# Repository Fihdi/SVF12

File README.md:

# 8hp 12dB/Oct Voltage Controlled state-variable Filter

# Features
- Two  Inputs **IN** (DC-coupled, allows for audio and CV processing)
- Volt per octave Input **V/O**
- Ping Input **PING**
- Self-Resonance switch **FILT/OSC**
- Lowpass **LP** Bandpass **BP** Bandstop(Notch) **BS** and Highpass **HP** outputs 

# Oscillator mode
The module can be switched from Filter mode (Switch in the **FILT** position) to Oscillator mode (Switch in the **OSC** position), turning the module into a musical sine-cosine quadrature VCO. This can produce clean sine waves on the **BP**, **BS** and **LP** outputs with no input, a mode called self-oscillation. The sinusoidal signals of  **BP** and **HP** are phase-shifted 0, 90 and 180 degrees.

.Inverting the **BP** signal and sending it back into a state variable filter it starts to self-oscillate, albeit with no limiting. Switching from **FILT** to **OSC** changes the **RES** knob from a variable voltage divider to an attenuverter with diode-clipping. With a trimmer on the back of the module, the **V/O** input can be tuned to allow for volt per octave tracking

# Ping Input
By sending a rising-edge signal like a Gate or a short Pulse to the **PING** input, the filter core gets excited and creates a damped oscillation. The length of this oscillation is controlled by the resonance (**RES**) setting.

# Power
A standard 10-pin Eurorack power connector is used (Red Stripe indicates -12V (negative twelve volts)). The module is internally running on +/-9V to stabilise the volt per octave tracking.

# Sponsor
A big Thank You to [PCBWay](https://www.pcbway.com) for sponsoring the development and prototyping of this module! They have excellent build quality and I can recommend using their service to build your own projects! I used the "Black" soldermask and white silkscreen and the surface has very deep and glossy black finish.

Simply upload the Gerber and production files for the B-Board and 90% of the circuitry is done. Solder the final through-hole components and tightend the screws and you have a finished Eurorack module, ready to give your sounds a crunchy filter effect.

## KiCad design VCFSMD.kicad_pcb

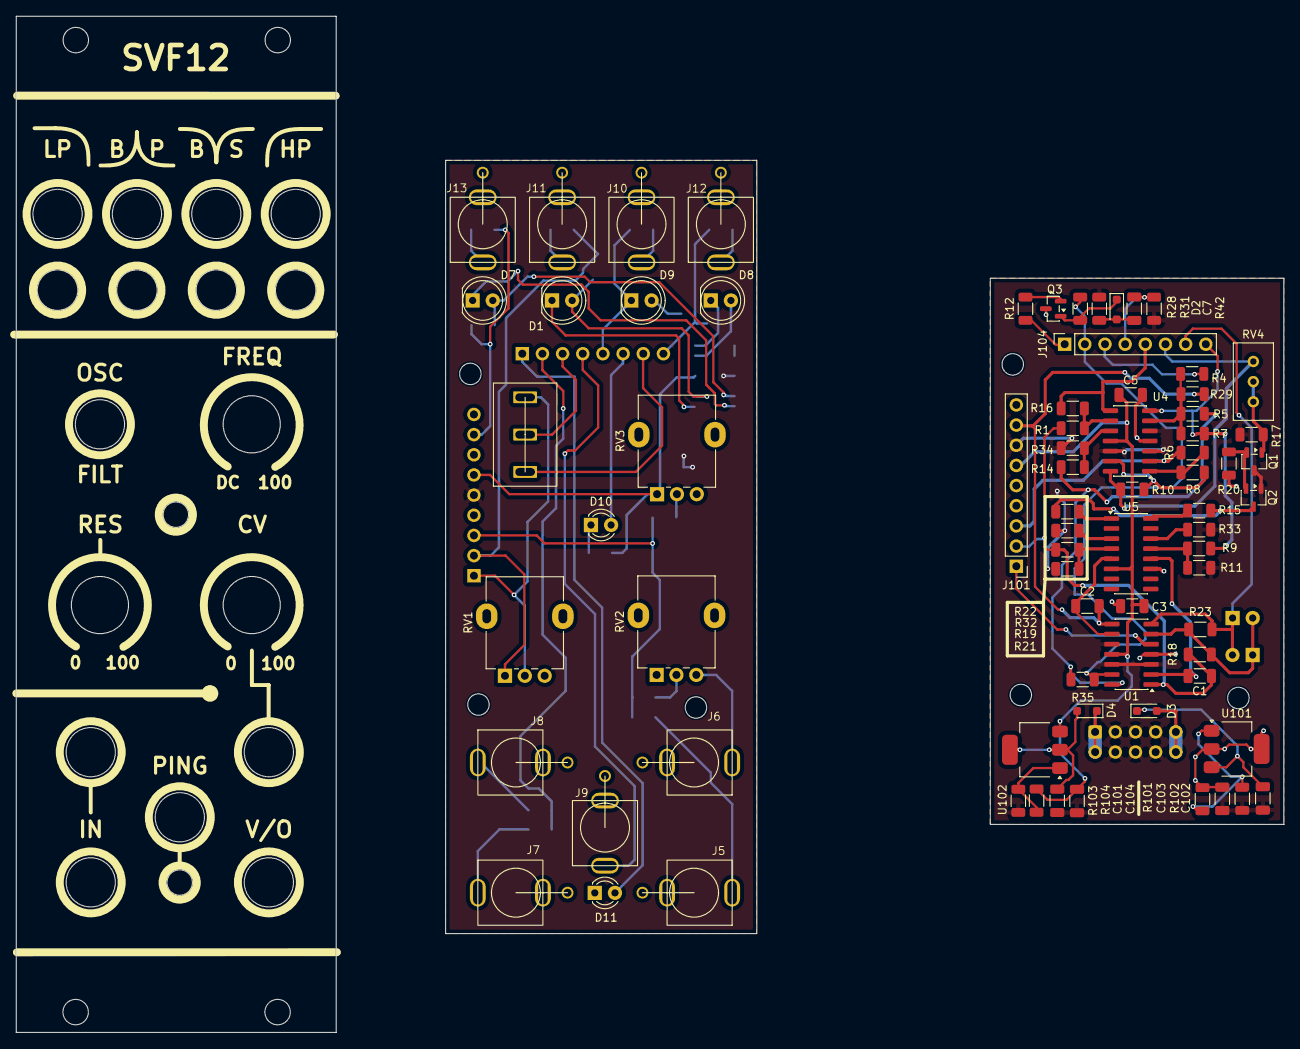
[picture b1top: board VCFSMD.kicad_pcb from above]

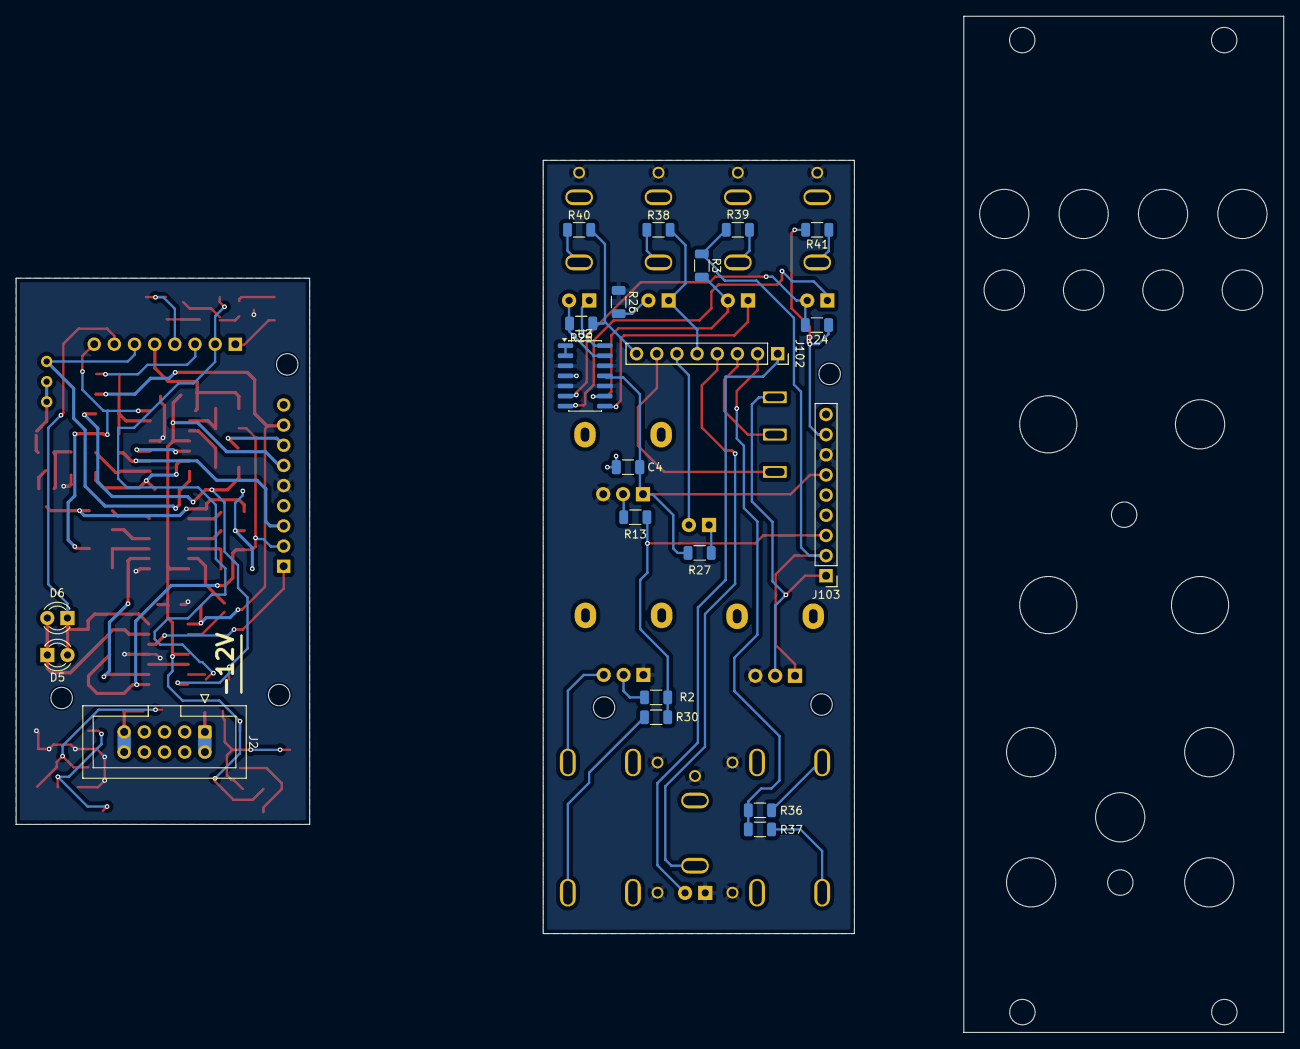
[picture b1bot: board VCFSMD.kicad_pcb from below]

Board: 2 copper layers, 159.7 x 128.0 mm, 95 parts (21 on the bottom side), 61 nets.

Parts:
C1, C2: 220pF; C_1206_3216Metric
C3, C4, C5: 100n; C_1206_3216Metric
C7: 10n; C_1206_3216Metric
C101, C102, C103, C104: 10u; C_1206_3216Metric
D1, D7, D8, D9: LED_Dual_Bidirectional; LED_D5.0mm
D2, D3, D4: 1N4148; D_SOD-323_HandSoldering
D5, D6, D10, D11: LED; LED_D3.0mm
J2: Conn_02x05_Odd_Even; IDC-Header_2x05_P2.54mm_Vertical
J5, J6, J7, J8, J9, J10, J11, J12, J13: AudioJack2; MonoTRS
J101, J103: Conn_01x09_Pin; PinHeader_1x09_P2.54mm_Vertical
J102, J104: Conn_01x08_Pin; PinSocket_1x08_P2.54mm_Vertical
Q1, Q2: BC857; SOT-23-3
Q3: BC847; SOT-23
R1, R2, R4, R5, R6, R7, R8, R10, R13, R14, R16, R18, R28, R29, R30, R31, R34, R35, R36, R37, R42: 100k; R_1206_3216Metric
R3, R12, R15, R22, R24, R25, R26, R27: 2k2; R_1206_3216Metric
R9, R19: 200k; R_1206_3216Metric
R11, R17, R21, R32, R33, R38, R39, R40, R41, R101, R104: 1k; R_1206_3216Metric
R20: 10k; R_1206_3216Metric
R23: 47k; R_1206_3216Metric
R102, R103: 6k2; R_1206_3216Metric
RV1, RV2, RV3: 100k; Potentiometer_Alpha_RD901F-40-00D_Single_Vertical
RV4: 100k; Potentiometer_Bourns_3296W_Vertical
SW1: SW_SPDT; Switch
U1, U3, U4: TL074; SOIC-14_3.9x8.7mm_P1.27mm
U5: LM13700; SOIC-16_3.9x9.9mm_P1.27mm
U101: LM317_SOT-223; SOT-223-3_TabPin2
U102: LM337_SOT223; SOT-223-3_TabPin2

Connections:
+9V: C3.2, C4.2, C5.2, C103.1, J101.5, J103.5, Q3.3 (C), R20.2, R101.1, U1.4 (V+), U3.4 (V+), U4.4 (V+), U5.11 (V+), U101.2 (VO)
+12V: C102.2, D3.1 (K), U101.3 (VI)
-9V: C3.1, C4.1, C5.1, C104.1, J101.6, J103.6, R27.1, R104.2, RV3.1, U1.11 (V-), U3.11 (V-), U4.11 (V-), U5.6 (V-), U102.3 (VO)
-12V: C101.1, D4.2 (A), U102.2 (VI)
AUDIN: R5.1, R14.2, R35.1, U1.14
AUDSUM: J102.2, J104.2, R28.2, R35.2, R36.1, R37.1, U1.13 (-)
BP: C1.2, J101.2, J103.2, R1.2, R3.1, R18.2, R19.1, R39.2, RV1.1, U1.1
BP_INV: D5.2 (A), D6.1 (K), J102.7, J104.7, R23.1, SW1.1 (A), U1.7
BP_POT: J101.1, J103.1, RV1.2, SW1.3 (C), U1.5 (+)
GND: C101.2, C102.1, C103.2, C104.2, D11.1 (K), J2.3, J2.4, J2.5, J2.6, J2.7, J2.8, J5.S, J6.S, J7.S, J8.S, J9.S, J10.S, J11.S, J12.S, J13.S, J101.7, J103.7, Q1.3 (C), Q2.1 (B), R11.1, R17.1, R21.1, R26.1, R31.2, R32.1, R33.1, R34.2, R42.2, R102.2, R103.1, RV1.3, RV2.1, RV3.3, U1.3 (+), U1.10 (+), U1.12 (+), U3.3 (+), U3.5 (+), U3.10 (+), U3.12 (+), U4.3 (+), U4.5 (+), U4.12 (+)
HP: J102.8, J104.8, R7.2, R9.1, R25.1, R40.2, U4.7
LED: D10.2 (A), J102.6, J104.6, R10.2, RV4.1, U4.14
LP: C2.2, J101.8, J103.8, R24.1, R29.1, R41.2, U1.8
unnamed: D1.2 (AK), R3.2, U3.9 (-)
unnamed: D1.1 (KA), U3.8
unnamed: C7.1, D2.2 (A), R31.1
unnamed: D2.1 (K), Q3.1 (B), R28.1
unnamed: D3.2 (A), J2.9, J2.10
unnamed: D4.1 (K), J2.1, J2.2
unnamed: D5.1 (K), D6.2 (A), R18.1, R23.2, U1.6 (-)
unnamed: D7.2 (AK), R24.2, U3.6 (-)
unnamed: D7.1 (KA), U3.7
unnamed: D8.2 (AK), R25.2, U3.13 (-)
unnamed: D8.1 (KA), U3.14
unnamed: D9.2 (AK), R26.2
unnamed: D10.1 (K), R27.2
unnamed: J5.T, R30.1
unnamed: J6.T, RV2.3
unnamed: J7.T, R37.2
unnamed: J8.T, R36.2
unnamed: J10.T, R38.1
unnamed: J11.T, R39.1
unnamed: J12.T, R40.1
unnamed: J13.T, R41.1
unnamed: Q1.1 (B), R17.2, RV4.2, RV4.3
unnamed: Q1.2 (E), Q2.2 (E), R20.1
unnamed: Q2.3 (C), R15.1, R22.1
unnamed: Q3.2 (E), R12.2
unnamed: R2.1, RV2.2
unnamed: R6.2, R8.1, U4.1
unnamed: R13.1, RV3.2
unnamed: R15.2, U5.16
unnamed: R22.2, U5.1
unnamed: C1.1, U1.2 (-), U5.12
unnamed: C2.1, U1.9 (-), U5.5
unnamed: U3.1, U3.2 (-)
unnamed: R14.1, R34.1, U4.10 (+)
unnamed: R1.1, R16.2, U4.9 (-)
unnamed: R8.2, R10.1, U4.13 (-)
unnamed: R33.2, U5.14 (+)
unnamed: R9.2, R11.2, U5.13 (-)
unnamed: R32.2, U5.3 (+)
unnamed: R19.2, R21.2, U5.4 (-)
unnamed: R101.2, R102.1, U101.1 (ADJ)
unnamed: R103.2, R104.1, U102.1 (ADJ)
OUT_BS: D9.1 (KA), J102.5, J104.5, R16.1, R38.2, U4.8
PINGIN: C7.2, J9.T, J102.4, J104.4, R42.1
PINGLED: D11.2 (A), J102.1, J104.1, R12.1
SW12: J102.3, J104.3, R4.1, SW1.2 (B)
VGNDAUD: R4.2, R5.2, R7.1, R29.2, U4.6 (-)
VGNDCV: J101.3, J103.3, R2.2, R6.1, R13.2, R30.2, U4.2 (-)

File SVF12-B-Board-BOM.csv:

"Reference","Qty","Value","DNP","Exclude from BOM","Exclude from Board","Footprint","Datasheet"
"C1,C2","2","220pF","","","","Capacitor_SMD:C_1206_3216Metric","~"
"C3,C5","2","100n","","","","Capacitor_SMD:C_1206_3216Metric","~"
"C7","1","10n","","","","Capacitor_SMD:C_1206_3216Metric","~"
"C101,C102,C103,C104","4","10u","","","","Capacitor_SMD:C_1206_3216Metric","~"
"D2,D3,D4","3","1N4148","","","","Diode_SMD:D_SOD-323_HandSoldering","https://www.diodes.com/assets/Datasheets/ds30396.pdf"
"D5,D6","2","LED","","","","LED_THT:LED_D3.0mm","~"
"J2","1","Conn_02x05_Odd_Even","","","","Connector_IDC:IDC-Header_2x05_P2.54mm_Vertical","~"
"J101","1","Conn_01x09_Pin","","","","Connector_PinHeader_2.54mm:PinHeader_1x09_P2.54mm_Vertical","~"
"J104","1","Conn_01x08_Pin","","","","Connector_PinSocket_2.54mm:PinSocket_1x08_P2.54mm_Vertical","~"
"Q1,Q2","2","BC857","","","","Package_TO_SOT_SMD:SOT-23-3","https://www.onsemi.com/pub/Collateral/BC860-D.pdf"
"Q3","1","BC847","","","","Package_TO_SOT_SMD:SOT-23","http://www.infineon.com/dgdl/Infineon-BC847SERIES_BC848SERIE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"
"R1,R4,R5,R6,R7,R8,R10,R14,R16,R18,R28,R29,R31,R34,R35,R42","16","100k","","","","Resistor_SMD:R_1206_3216Metric","~"
"R9,R19","2","200k","","","","Resistor_SMD:R_1206_3216Metric","~"
"R11,R17,R21,R32,R33,R101,R104","7","1k","","","","Resistor_SMD:R_1206_3216Metric","~"
"R12,R15,R22","3","2k2","","","","Resistor_SMD:R_1206_3216Metric","~"
"R20","1","10k","","","","Resistor_SMD:R_1206_3216Metric","~"
"R23","1","47k","","","","Resistor_SMD:R_1206_3216Metric","~"
"R102,R103","2","6k2","","","","Resistor_SMD:R_1206_3216Metric","~"
"RV4","1","100k","","","","Potentiometer_THT:Potentiometer_Bourns_3296W_Vertical","~"
"U1,U4","2","TL074","","","","Package_SO:SOIC-14_3.9x8.7mm_P1.27mm","http://www.ti.com/lit/ds/symlink/tl071.pdf"
"U5","1","LM13700","","","","Package_SO:SOIC-16_3.9x9.9mm_P1.27mm","http://www.ti.com/lit/ds/symlink/lm13700.pdf"
"U101","1","LM317_SOT-223","","","","Package_TO_SOT_SMD:SOT-223-3_TabPin2","http://www.ti.com/lit/ds/symlink/lm317.pdf"
"U102","1","LM337_SOT223","","","","Package_TO_SOT_SMD:SOT-223-3_TabPin2","http://www.ti.com/lit/ds/symlink/lm337-n.pdf"
